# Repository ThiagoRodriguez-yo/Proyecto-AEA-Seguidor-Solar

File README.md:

# Proyecto-AEA-Seguidor-Solar
Este proyecto consiste en la realización de un seguidor solar usando de base servomotores para lograr el movimiento del panel

## Colaboradores

- **Sebastián Pérez**
- **Ramiro Trejo**
- **Rodríguez Thiago**

## Componentes

-  1 AMS1117 5V
-  1 ATtiny 85
-  2 Fotoresistencias LDR (Light Dependent Resistor)
-  2 Servomotor SG90
-  1 Bateria Lipo 2S 450mAh

## Complementos de estudio

Para su diseño de PCB y 3D se utilizara software como KiCad y AutoDesk Fusion y Proteus para su simulacion

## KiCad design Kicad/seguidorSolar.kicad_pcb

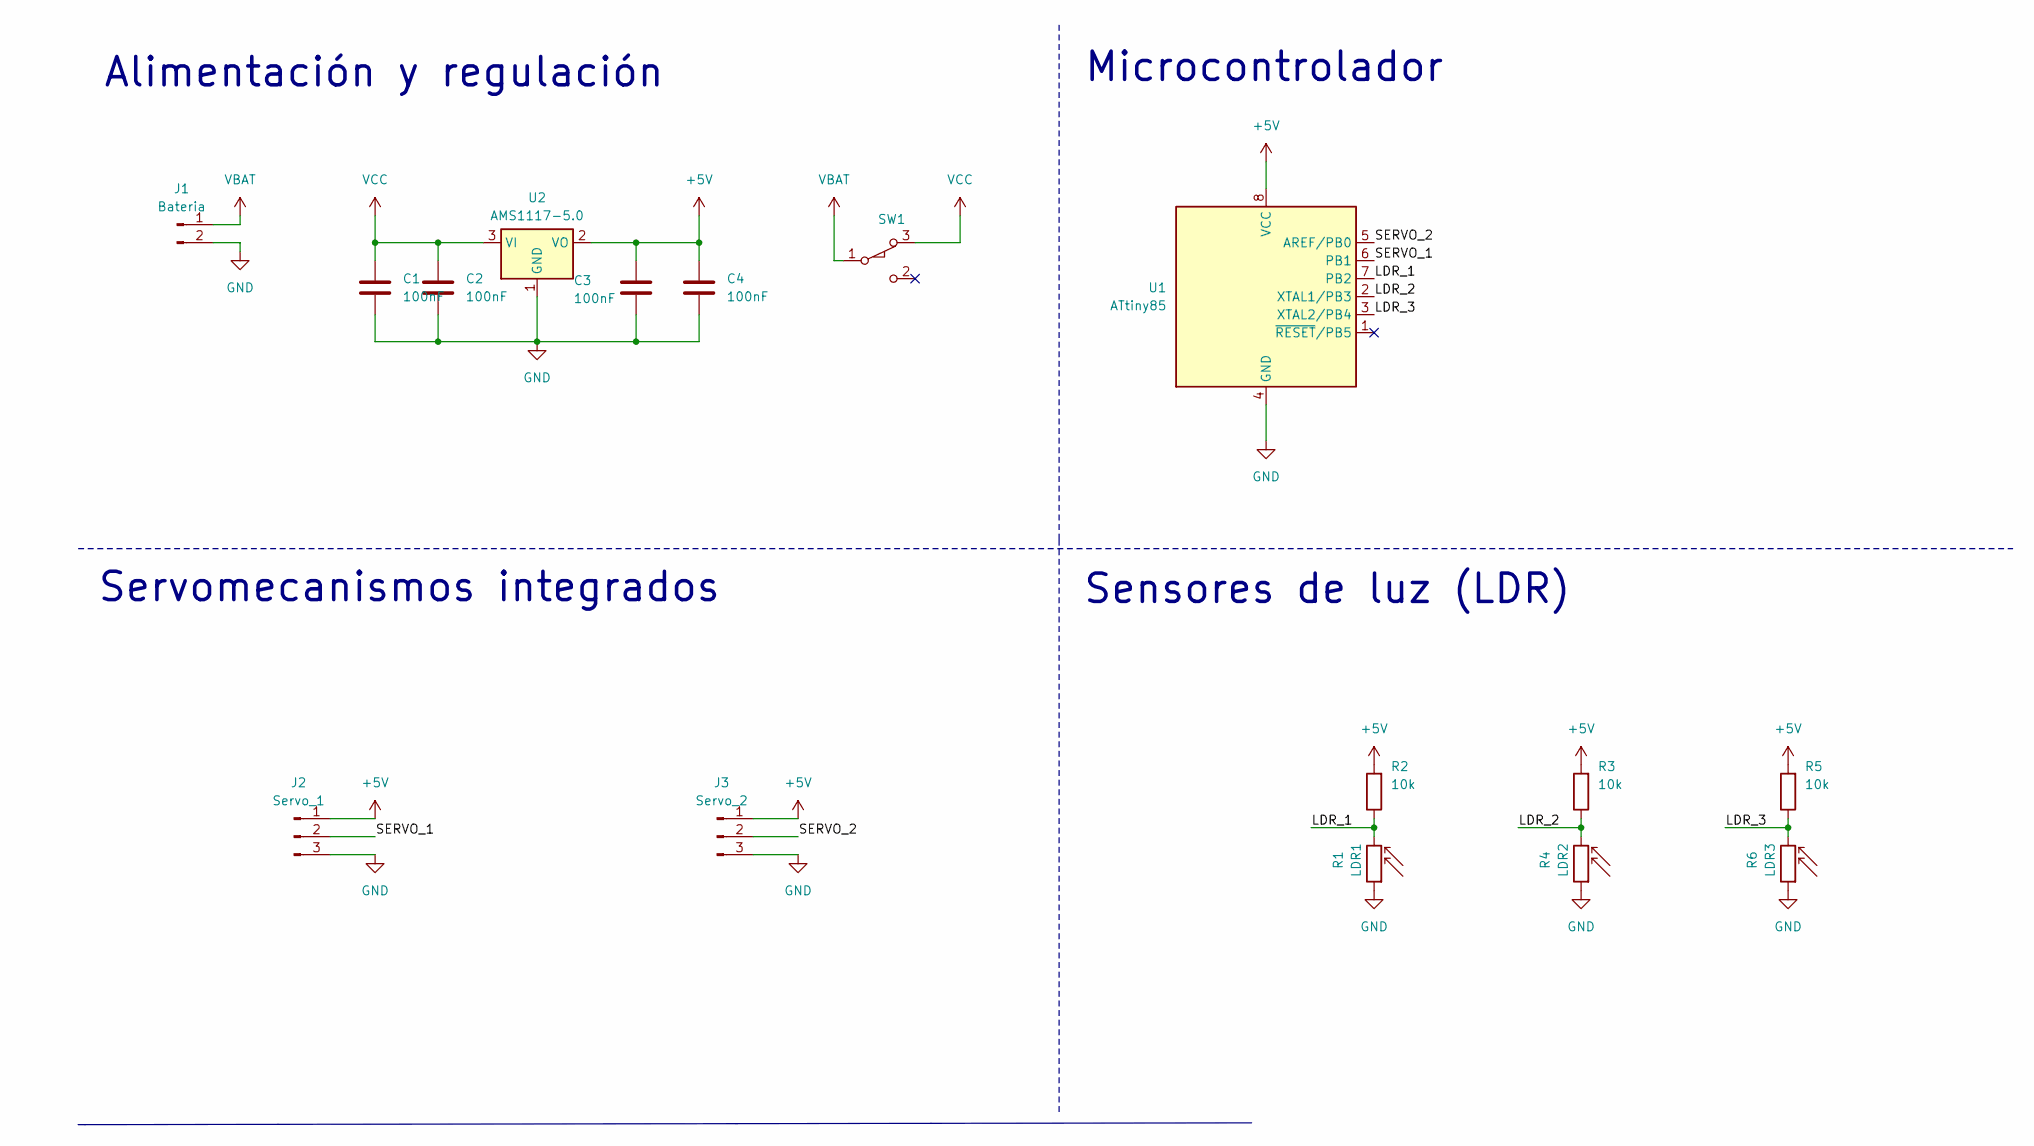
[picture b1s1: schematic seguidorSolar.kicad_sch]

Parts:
C1, C2, C3, C4: 100nF; C_0805_2012Metric_Pad1.18x1.45mm_HandSolder
J1: Bateria; XT30 connector
J2: Servo_1; PinHeader_1x03_P2.54mm_Vertical
J3: Servo_2; PinHeader_1x03_P2.54mm_Vertical
R1: LDR1; R_LDR_5.1x4.3mm_P3.4mm_Vertical
R2, R3, R5: 10k; R_1206_3216Metric_Pad1.30x1.75mm_HandSolder
R4: LDR2; R_LDR_5.1x4.3mm_P3.4mm_Vertical
R6: LDR3; R_LDR_5.1x4.3mm_P3.4mm_Vertical
SW1: SW_SPDT_XKB_DMx-xxxx-1; PinHeader_1x03_P2.54mm_Vertical
U1: ATtiny85; DIP-8_W7.62mm
U2: AMS1117-5.0; SOT-223-3_TabPin2

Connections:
+5V: C3.1, C4.1, J2.1, J3.1, R2.2, R3.2, R5.2, U1.8 (VCC), U2.2 (VO)
/LDR_1: R1.2, R2.1, U1.7 (PB2)
/LDR_2: R3.1, R4.2, U1.2 (XTAL1/PB3)
/LDR_3: R5.1, R6.2, U1.3 (XTAL2/PB4)
/SERVO_1: J2.2, U1.6 (PB1)
/SERVO_2: J3.2, U1.5 (AREF/PB0)
GND: C1.2, C2.2, C3.2, C4.2, J1.2, J2.3, J3.3, R1.1, R4.1, R6.1, U1.4 (GND), U2.1 (GND)
VBAT: J1.1, SW1.1 (A)
VCC: C1.1, C2.1, SW1.3 (C), U2.3 (VI)

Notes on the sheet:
Microcontrolador
Alimentación y regulación
Servomecanismos integrados
Sensores de luz (LDR)

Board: 2 copper layers, 16 parts (0 on the bottom side), 9 nets, no tracks yet.
